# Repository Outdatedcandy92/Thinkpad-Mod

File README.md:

# Thinkpad Mod

A small board that I designed to be embedded inside my Thinkpad X1 Carbon Gen 7 laptop. It features a MCU on board along with a ton of sensors for data logging and an RGB led placed to shine on the red dot that's on the Thinkpad Logo.

---
## Schematic

The project's KiCad files can be found under `/PCB/kicad`.

---
## PCB

---
## BOM

| Name          | Description                                                                                       | Quantity | Price  | Shipping |
| ------------- | ------------------------------------------------------------------------------------------------- | -------- | ------ | -------- |
| Componenets   | Componenets from LCSC. detailed part breakdown [here](./production/Thinkpad_Mod_Rev_1.0.0_bom.csv) | -        | $26.63 | $12.62   |
| PCB+Stencil   | PCB and Stencil from JLCPCB                                                                       | -        | $5.10  | $8.35    |
| **Sub Total** |                                                                                                   |          | $31.73 | $20.97   |
| **Total**     |                                                                                                   |          | $52.7  |          |

---

## License

This project is licensed under the CERN Open Hardware Licence Version 2 Weakly Reciprocal [(CERN OHL W)](LICENSE.txt)

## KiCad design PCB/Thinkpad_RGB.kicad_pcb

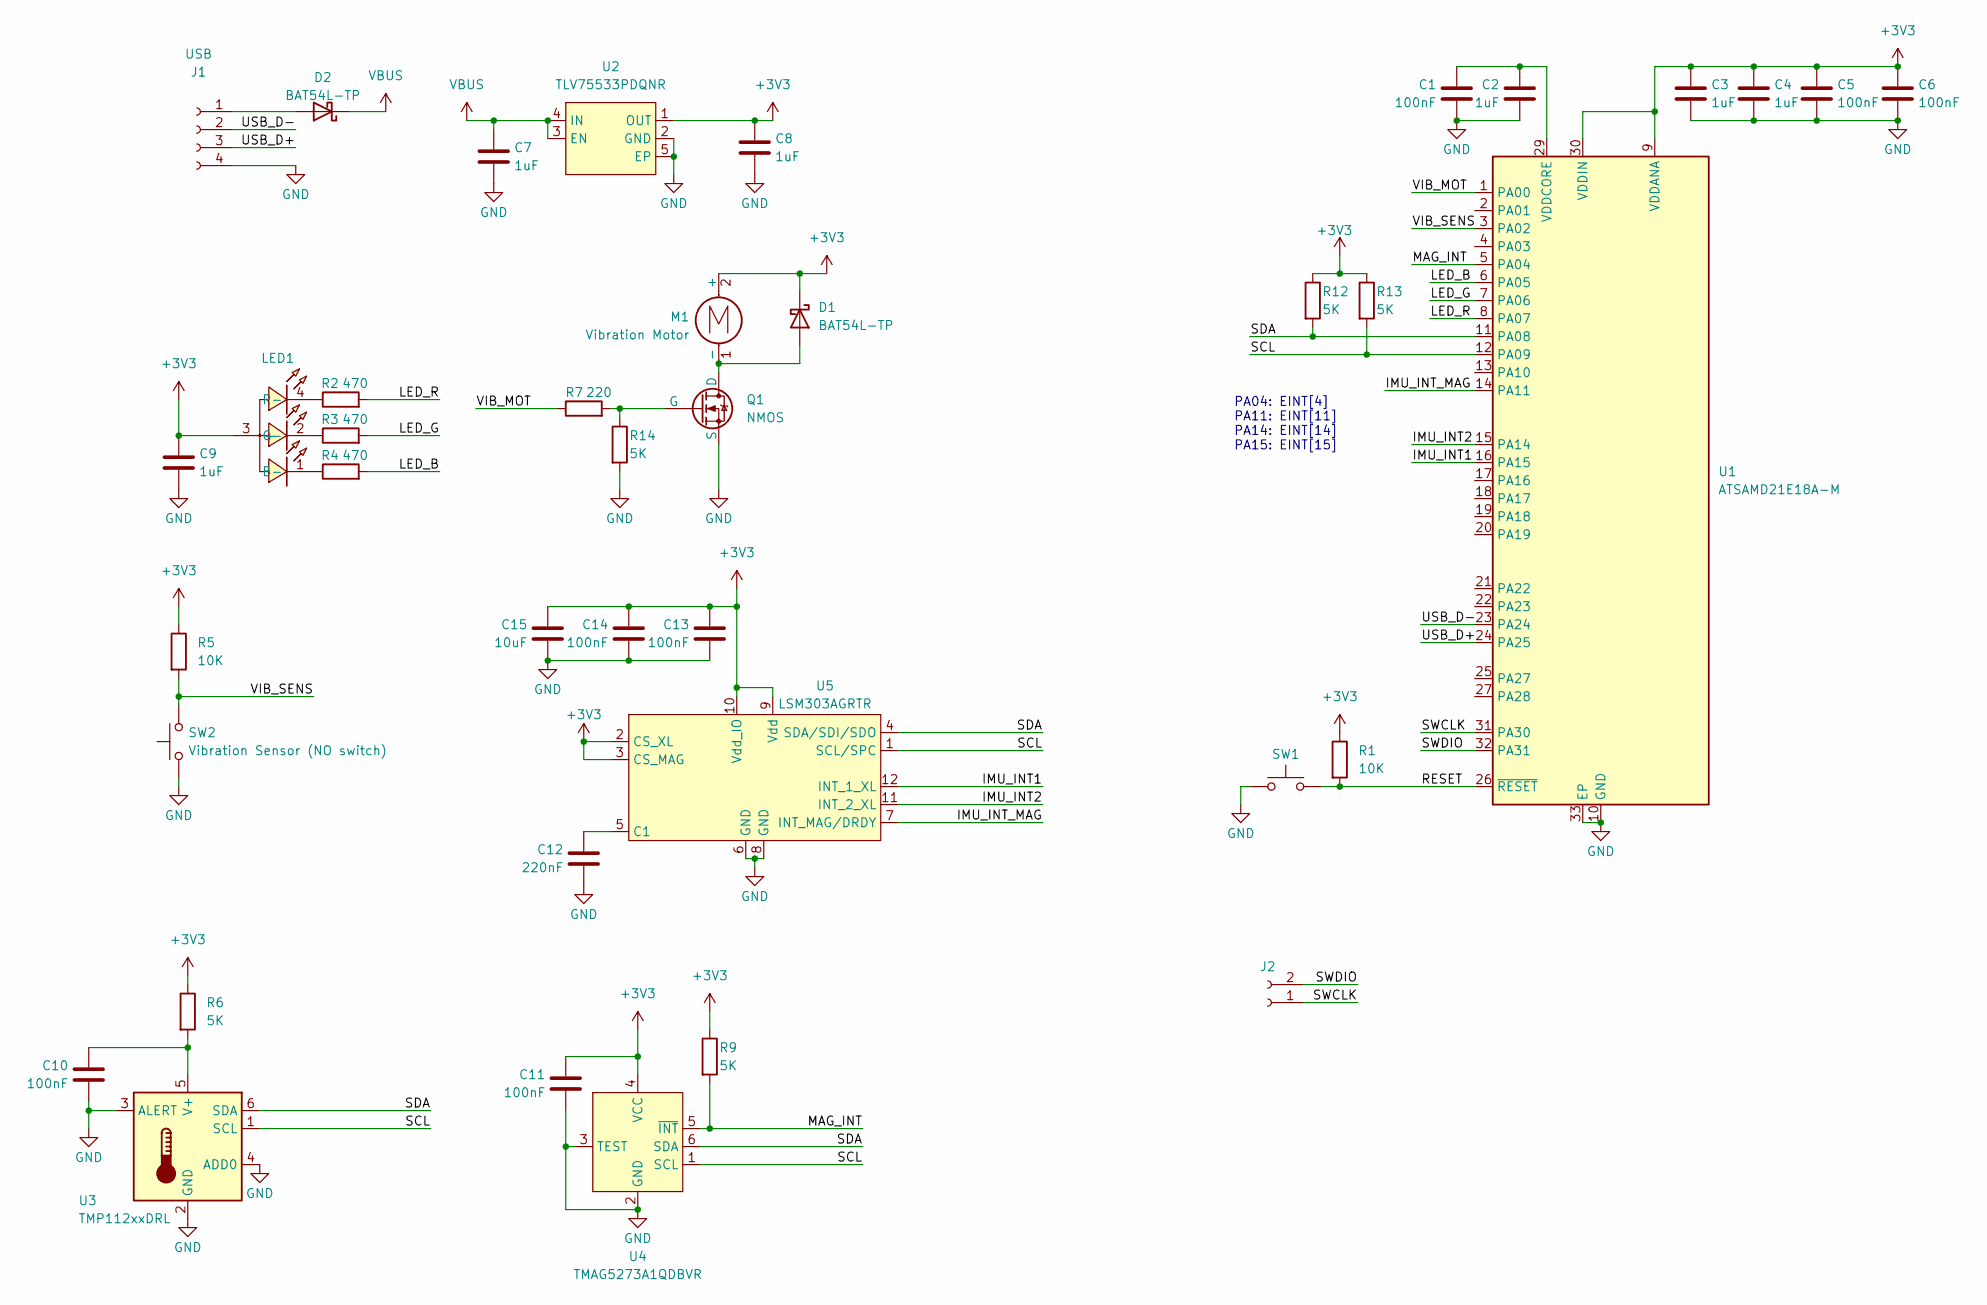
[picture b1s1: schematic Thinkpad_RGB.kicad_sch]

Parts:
C1, C5, C6, C10, C11, C13, C14: 100nF; C_0402_1005Metric; LCSC Part C1525
C2, C3, C4, C7, C8, C9: 1uF; C_0402_1005Metric; LCSC Part C52923
C12: 220nF; C_0402_1005Metric; LCSC Part C16772
C15: 10uF; C_0402_1005Metric; LCSC Part C315248
D1, D2: BAT54L-TP; D_SOD-882; LCSC Part C587155
J1: USB; CONN-SMD_4P-P1.00_SM04B-SRSS-TB-LF-SN; LCSC Part C160404
J2: Conn_01x02_Socket; CONN-SMD_2P-P1.00_SM02B-SRSS-TB-LF-SN; LCSC Part C160402
LED1: XL-3806RGBC-4L; LED-SMD_4P-L3.8-W1.0_XL-3806RGBC-4L; LCSC Part C2843779
M1: Vibration Motor; CONN-SMD_2P-P1.00_SM02B-SRSS-TB-LF-SN; LCSC Part C160402
Q1: NMOS; SOT-23; LCSC Part C10488
R1, R5: 10K; R_0402_1005Metric; LCSC Part C25128
R2, R3, R4: 470; R_0402_1005Metric; LCSC Part C25900
R6, R9, R12, R13, R14: 5K; R_0402_1005Metric; LCSC Part C25905
R7: 220; R_0402_1005Metric; LCSC Part C25091
SW1: SW_Push; R_0805_2012Metric
SW2: Vibration Sensor (NO switch); R_0805_2012Metric; LCSC Part C42371121
U1: ATSAMD21E18A-M; QFN-32-1EP_5x5mm_P0.5mm_EP3.6x3.6mm; LCSC Part C2052801
U2: TLV75533PDQNR; X2SON-4_L1.0-W1.0-P0.65-TL-EP; LCSC Part C2861882
U3: TMP112xxDRL; SOT-563; LCSC Part C28927
U4: TMAG5273A1QDBVR; SOT-23-6_L2.9-W1.6-P0.95-LS2.8-BR; LCSC Part C3716049
U5: LSM303AGRTR; LGA-12_L2.0-W2.0-P0.50-BL; LCSC Part C126671

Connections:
+3V3: C3.1, C4.1, C5.1, C6.1, C8.1, C9.1, C11.1, C13.1, C14.1, C15.1, D1.1 (K), LED1.3 (+), M1.2 (+), R1.1, R5.1, R6.1, R9.1, R12.1, R13.1, U1.9 (VDDANA), U1.30 (VDDIN), U2.1 (OUT), U4.4 (VCC), U5.2 (CS_XL), U5.3 (CS_MAG), U5.9 (Vdd), U5.10 (Vdd_IO)
/IMU_INT1: U1.16 (PA15), U5.12 (INT_1_XL)
/IMU_INT2: U1.15 (PA14), U5.11 (INT_2_XL)
/IMU_INT_MAG: U1.14 (PA11), U5.7 (INT_MAG/DRDY)
/LED_B: R4.2, U1.6 (PA05)
/LED_G: R3.2, U1.7 (PA06)
/LED_R: R2.2, U1.8 (PA07)
/MAG_INT: R9.2, U1.5 (PA04), U4.5 (~INT)
/RESET: R1.2, SW1.2, U1.26 (~RESET)
/SCL: R13.2, U1.12 (PA09), U3.1 (SCL), U4.1 (SCL), U5.1 (SCL/SPC)
/SDA: R12.2, U1.11 (PA08), U3.6 (SDA), U4.6 (SDA), U5.4 (SDA/SDI/SDO)
/SWCLK: J2.1, U1.31 (PA30)
/SWDIO: J2.2, U1.32 (PA31)
/USB_D+: J1.3, U1.24 (PA25)
/USB_D-: J1.2, U1.23 (PA24)
/VIB_MOT: R7.1, U1.1 (PA00)
/VIB_SENS: R5.2, SW2.2, U1.3 (PA02)
GND: C1.2, C2.2, C3.2, C4.2, C5.2, C6.2, C7.2, C8.2, C9.2, C10.2, C11.2, C12.2, C13.2, C14.2, C15.2, J1.4, Q1.3 (S), R14.2, SW1.1, SW2.1, U1.10 (GND), U1.28 (GND), U1.33 (EP), U2.2 (GND), U2.5 (EP), U3.2 (GND), U3.3 (ALERT), U3.4 (ADD0), U4.2 (GND), U4.3 (TEST), U5.6 (GND), U5.8 (GND)
unnamed: D1.2 (A), M1.1 (-), Q1.1 (D)
unnamed: D2.2 (A), J1.1
unnamed: LED1.1 (B-), R4.1
unnamed: LED1.2 (G-), R3.1
unnamed: LED1.4 (R-), R2.1
unnamed: Q1.2 (G), R7.2, R14.1
unnamed: C1.1, C2.1, U1.29 (VDDCORE)
unnamed: C10.1, R6.2, U3.5 (V+)
unnamed: C12.1, U5.5 (C1)
VBUS: C7.1, D2.1 (K), U2.3 (EN), U2.4 (IN)

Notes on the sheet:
PA04: EINT[4] PA11: EINT[11] PA14: EINT[14] PA15: EINT[15]

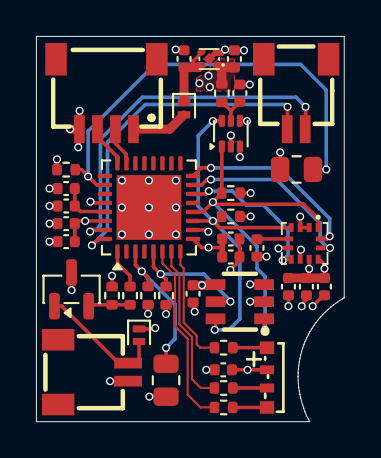
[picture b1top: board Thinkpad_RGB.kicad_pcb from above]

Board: 4 copper layers, 17.1 x 21.4 mm, 40 parts (0 on the bottom side), 28 nets.

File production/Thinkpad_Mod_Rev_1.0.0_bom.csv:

"Reference","Qty","Value","Footprint","LCSC Part"
"C1,C5,C6,C10,C11,C13,C14","7","100nF","Capacitor_SMD:C_0402_1005Metric","C1525"
"C2,C3,C4,C7,C8,C9","6","1uF","Capacitor_SMD:C_0402_1005Metric","C52923"
"C12","1","220nF","Capacitor_SMD:C_0402_1005Metric","C16772"
"C15","1","10uF","Capacitor_SMD:C_0402_1005Metric","C315248"
"D1,D2","2","BAT54L-TP","Diode_SMD:D_SOD-882","C587155"
"J1","1","USB","easyeda2kicad:CONN-SMD_4P-P1.00_SM04B-SRSS-TB-LF-SN","C160404"
"J2","1","Conn_01x02_Socket","easyeda2kicad:CONN-SMD_2P-P1.00_SM02B-SRSS-TB-LF-SN","C160402"
"LED1","1","XL-3806RGBC-4L","easyeda2kicad:LED-SMD_4P-L3.8-W1.0_XL-3806RGBC-4L","C2843779"
"M1","1","Vibration Motor","easyeda2kicad:CONN-SMD_2P-P1.00_SM02B-SRSS-TB-LF-SN","C160402"
"Q1","1","NMOS","Package_TO_SOT_SMD:SOT-23","C10488"
"R1,R5","2","10K","Resistor_SMD:R_0402_1005Metric","C25128"
"R2,R3,R4","3","470","Resistor_SMD:R_0402_1005Metric","C25900"
"R6,R9,R12,R13,R14","5","5K","Resistor_SMD:R_0402_1005Metric","C25905"
"R7","1","220","Resistor_SMD:R_0402_1005Metric","C25091"
"SW1","1","SW_Push","Resistor_SMD:R_0805_2012Metric","-"
"SW2","1","Vibration Sensor (NO switch)","Resistor_SMD:R_0805_2012Metric","C42371121"
"U1","1","ATSAMD21E18A-M","Package_DFN_QFN:QFN-32-1EP_5x5mm_P0.5mm_EP3.6x3.6mm","C2052801"
"U2","1","TLV75533PDQNR","easyeda2kicad:X2SON-4_L1.0-W1.0-P0.65-TL-EP","C2861882"
"U3","1","TMP112xxDRL","Package_TO_SOT_SMD:SOT-563","C28927"
"U4","1","TMAG5273A1QDBVR","easyeda2kicad:SOT-23-6_L2.9-W1.6-P0.95-LS2.8-BR","C3716049"
"U5","1","LSM303AGRTR","easyeda2kicad:LGA-12_L2.0-W2.0-P0.50-BL","C126671"

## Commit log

2026-01-22 rev 1
2026-01-29 cdn change
2026-01-29 cdn link fix
2026-02-12 bom readme
